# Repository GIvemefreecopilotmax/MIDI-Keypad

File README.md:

# MIDI Keypad

My custom MIDI keypad project, designed in KiCad using a Waveshare ESP32-S3-Zero.

## Features

- Seven capacitive touch keys
- Two sliding potentiometers
- One rotary encoder
- USB connection through the microcontroller

The keypad is intended to send MIDI notes and control messages once the firmware is implemented.

## Project files

- `MIDI-KEYPAD.kicad_sch` — circuit schematic
- `MIDI-KEYPAD.kicad_pcb` — PCB layout
- `MIDI-KEYPAD.kicad_pro` — KiCad project settings
- Gerber ZIP — exported PCB manufacturing files
- Screenshot — project preview

## Current progress

The schematic and PCB layout have been created. Firmware, physical assembly, and hardware testing are still pending. Manufacturing files still need final verification.

## Credits

Based on the MIDI Keypad guide by Kai Pereira:
https://github.com/KaiPereira/MIDI-Keypad

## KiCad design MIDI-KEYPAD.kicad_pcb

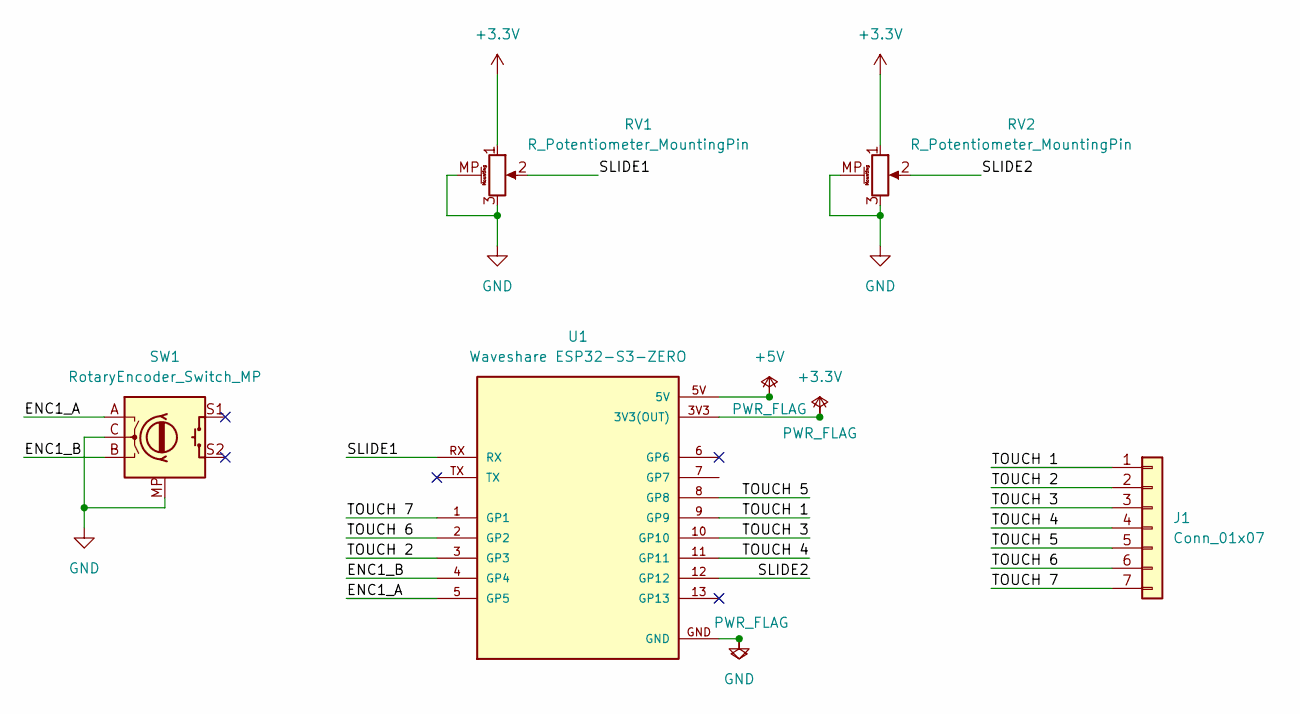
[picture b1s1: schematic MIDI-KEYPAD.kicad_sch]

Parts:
J1: Conn_01x07; MyKeypad
RV1, RV2: R_Potentiometer_MountingPin; Potentiometer_Bourns_PTA3043_Single_Slide
SW1: RotaryEncoder_Switch_MP; RotaryEncoder_Alps_EC11E-Switch_Vertical_H20mm_MountingHoles
U1: Waveshare ESP32-S3-ZERO; Waveshare ESP32-S3-Zero; PARTREV NA

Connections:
+3.3V: RV1.1, RV2.1, U1.3V3 (3V3(OUT))
+5V: U1.5V
/ENC1_A: SW1.A, U1.5 (GP5)
/ENC1_B: SW1.B, U1.4 (GP4)
/SLIDE1: RV1.2, U1.RX
/SLIDE2: RV2.2, U1.12 (GP12)
/TOUCH 1: J1.1, U1.9 (GP9)
/TOUCH 2: J1.2, U1.3 (GP3)
/TOUCH 3: J1.3, U1.10 (GP10)
/TOUCH 4: J1.4, U1.11 (GP11)
/TOUCH 5: J1.5, U1.8 (GP8)
/TOUCH 6: J1.6, U1.2 (GP2)
/TOUCH 7: J1.7, U1.1 (GP1)
GND: RV1.3, RV1.MP (MountPin), RV2.3, RV2.MP (MountPin), SW1.C, SW1.MP, U1.GND

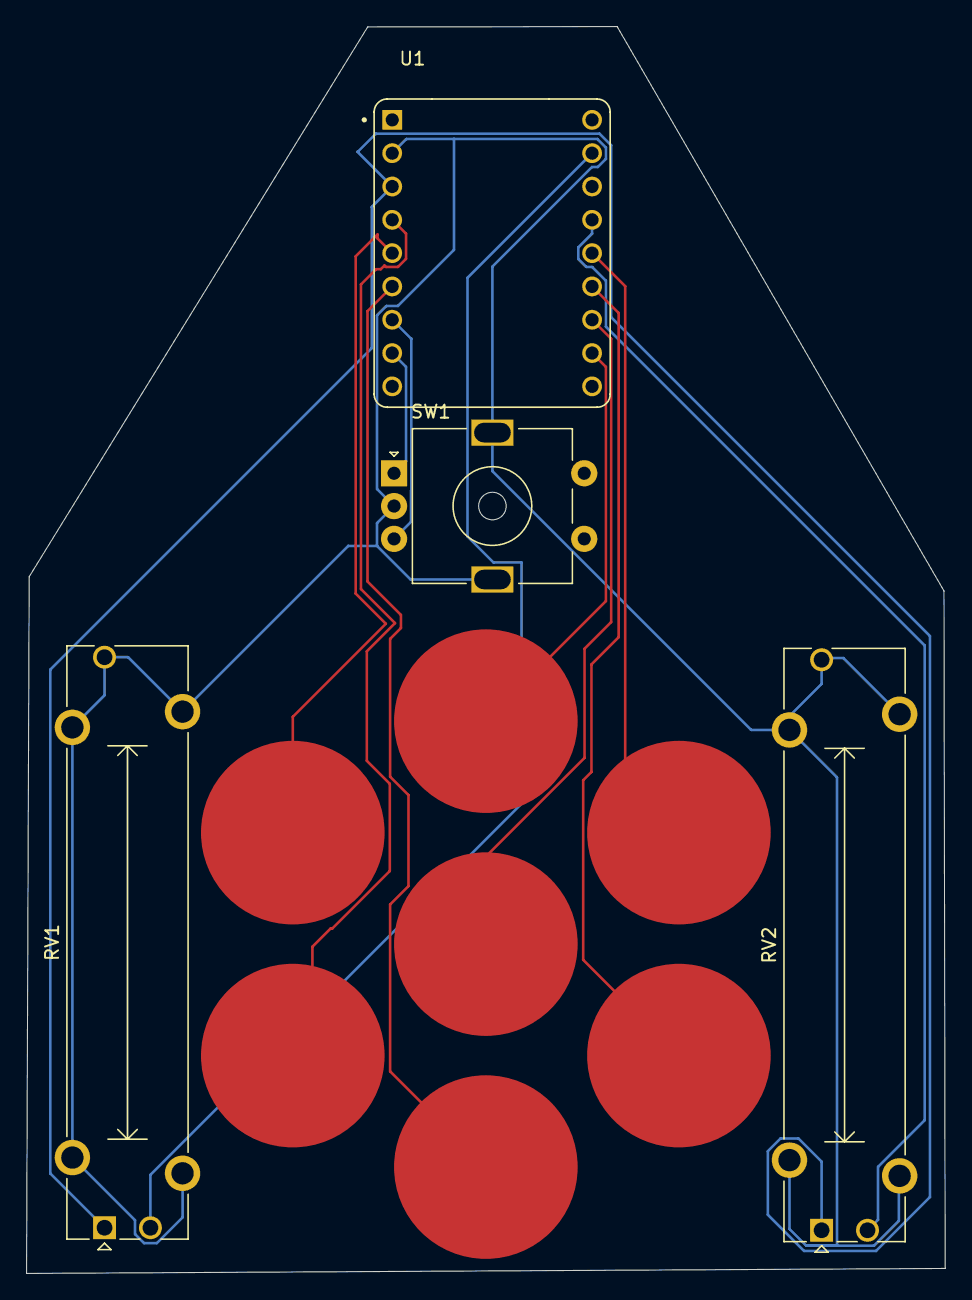
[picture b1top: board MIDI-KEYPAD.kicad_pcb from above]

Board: 2 copper layers, 70.0 x 95.1 mm, 5 parts (0 on the bottom side), 13 nets.
